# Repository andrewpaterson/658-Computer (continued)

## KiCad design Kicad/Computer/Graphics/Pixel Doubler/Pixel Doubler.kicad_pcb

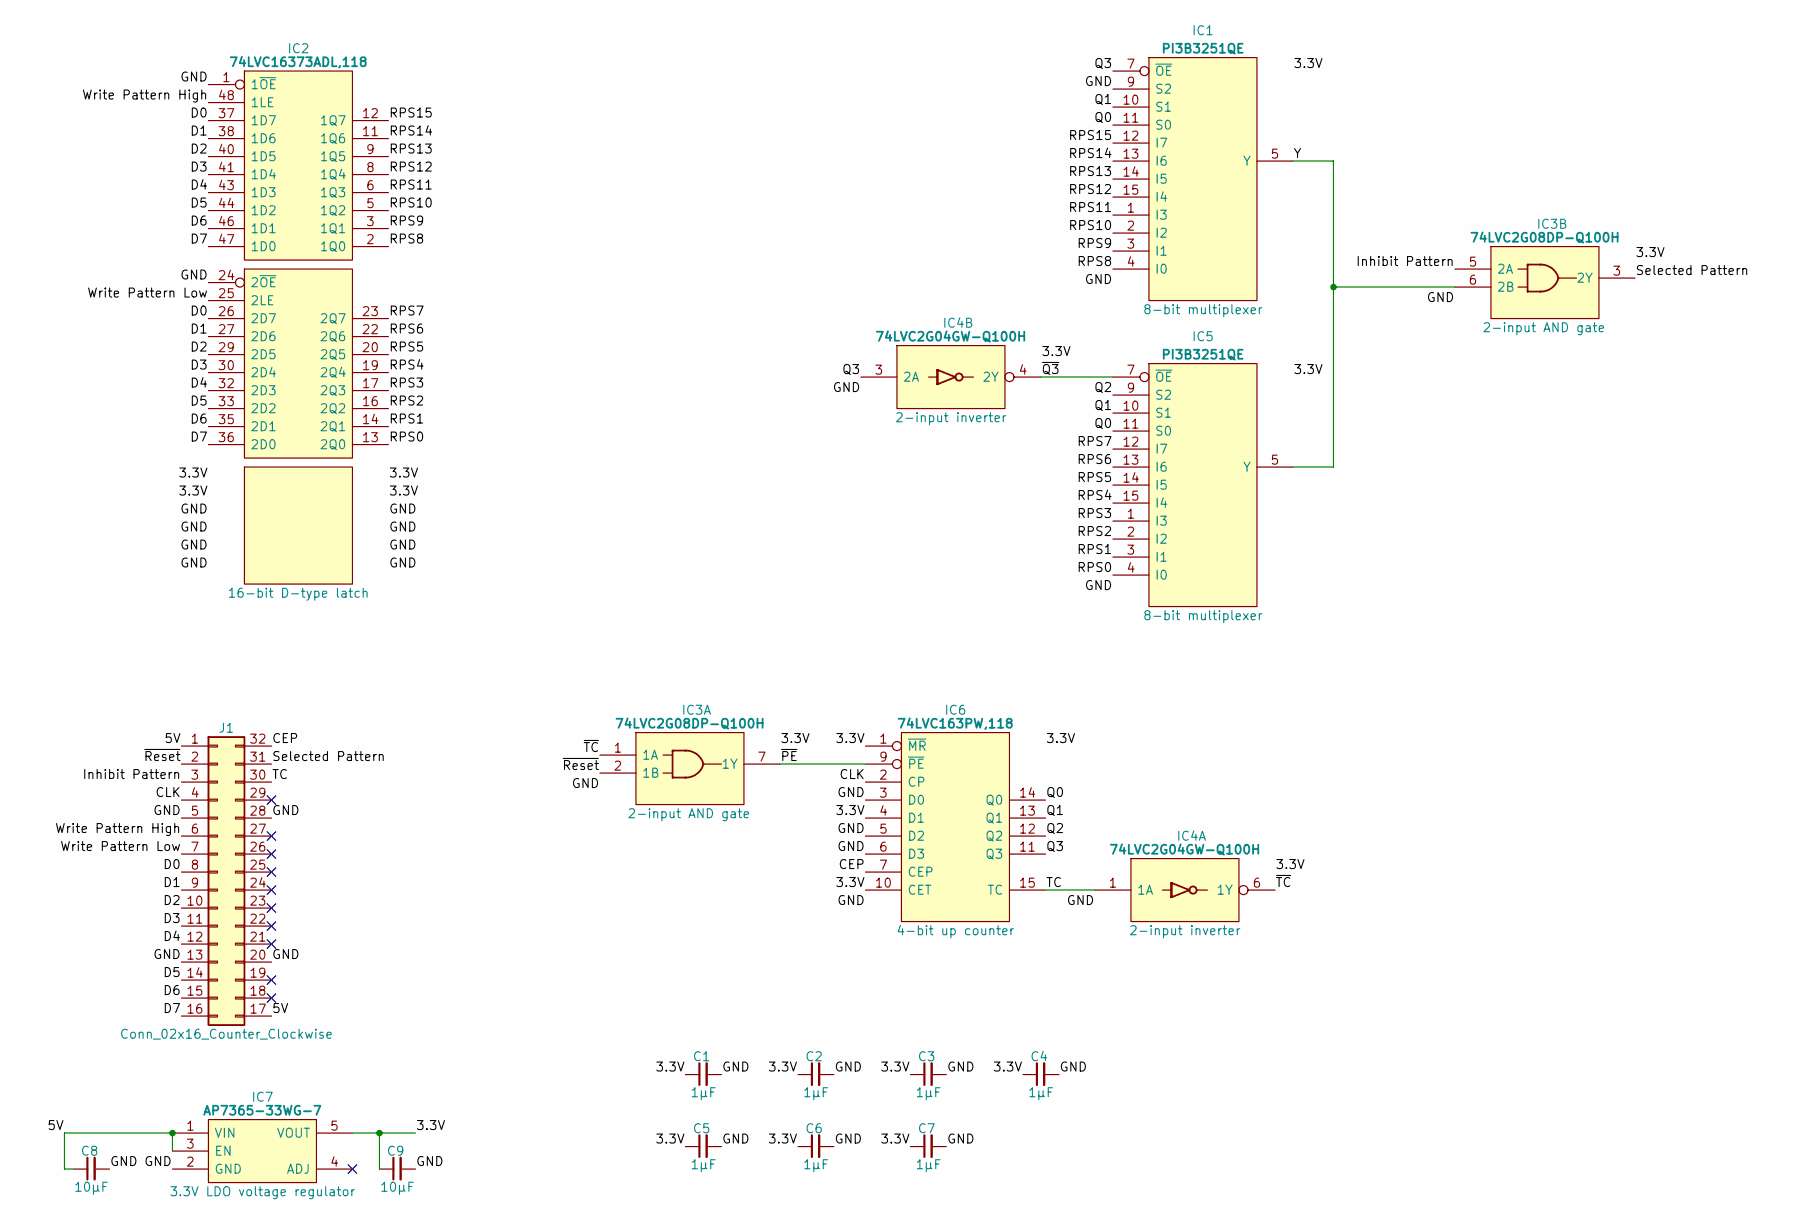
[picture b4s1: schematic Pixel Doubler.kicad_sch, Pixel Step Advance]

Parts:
C1, C2, C3, C4, C5, C6, C7: 1μF; C_0805
C8, C9: 10µF; C_0805
IC1, IC5: PI3B3251QE; SOP64P599X175-16N; Manufacturer_Part_Number PI3B3251QE; Mouser Part Number 729-PI3B3251QE
IC2: 74LVC16373ADL,118; SOP64P1025X280-48N; Mouser Part Number 771-LVC16373ADL118
IC3: 74LVC2G08DP-Q100H; SOP65P400X110-8N; Manufacturer_Part_Number 74LVC2G08DP-Q100H; Mouser Part Number 771-74LVC2G08DPQ100H
IC4: 74LVC2G04GW-Q100H; SOP65P210X110-6N; Manufacturer_Part_Number 74LVC2G04GW-Q100H; Mouser Part Number 771-74LVC2G04GWQ100H
IC6: 74LVC163PW,118; SOP65P640X110-16N; Mouser Part Number 771-74LVC163PW-T
IC7: AP7365-33WG-7; SOT95P285X130-5N; Manufacturer_Part_Number AP7365-33WG-7; Mouser Part Number 621-AP7365-33WG-7
J1: Conn_02x16_Counter_Clockwise; DIP-32_Board_W22.86mm

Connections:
/3.3V: C1.1, C2.1, C3.1, C4.1, C5.1, C6.1, C7.1, C9.1, IC1.16 (3V), IC2.7 (3V), IC2.18 (3V), IC2.31 (3V), IC2.42 (3V), IC3.8 (3V), IC4.5 (3V), IC5.16 (3V), IC6.1 (~MR), IC6.4 (D1), IC6.10 (CET), IC6.16 (3V), IC7.5 (VOUT)
/5V: C8.1, IC7.1 (VIN), IC7.3 (EN), J1.1, J1.17
/CEP: IC6.7 (CEP), J1.32
/CLK: IC6.2 (CP), J1.4
/D0: IC2.26 (2D7), IC2.37 (1D7), J1.8
/D1: IC2.27 (2D6), IC2.38 (1D6), J1.9
/D2: IC2.29 (2D5), IC2.40 (1D5), J1.10
/D3: IC2.30 (2D4), IC2.41 (1D4), J1.11
/D4: IC2.32 (2D3), IC2.43 (1D3), J1.12
/D5: IC2.33 (2D2), IC2.44 (1D2), J1.14
/D6: IC2.35 (2D1), IC2.46 (1D1), J1.15
/D7: IC2.36 (2D0), IC2.47 (1D0), J1.16
/GND: C1.2, C2.2, C3.2, C4.2, C5.2, C6.2, C7.2, C8.2, C9.2, IC1.8 (GND), IC1.9 (S2), IC2.1 (1~OE), IC2.4 (GND), IC2.10 (GND), IC2.15 (GND), IC2.21 (GND), IC2.24 (2~OE), IC2.28 (GND), IC2.34 (GND), IC2.39 (GND), IC2.45 (GND), IC3.4 (GND), IC4.2 (GND), IC5.8 (GND), IC6.3 (D0), IC6.5 (D2), IC6.6 (D3), IC6.8 (GND), IC7.2 (GND), J1.5, J1.13, J1.20, J1.28
/Inhibit Pattern: IC3.5 (2A), J1.3
/Q0: IC1.11 (S0), IC5.11 (S0), IC6.14 (Q0)
/Q1: IC1.10 (S1), IC5.10 (S1), IC6.13 (Q1)
/Q2: IC5.9 (S2), IC6.12 (Q2)
/Q3: IC1.7 (~OE), IC4.3 (2A), IC6.11 (Q3)
/RPS0: IC2.13 (2Q0), IC5.4 (I0)
/RPS1: IC2.14 (2Q1), IC5.3 (I1)
/RPS2: IC2.16 (2Q2), IC5.2 (I2)
/RPS3: IC2.17 (2Q3), IC5.1 (I3)
/RPS4: IC2.19 (2Q4), IC5.15 (I4)
/RPS5: IC2.20 (2Q5), IC5.14 (I5)
/RPS6: IC2.22 (2Q6), IC5.13 (I6)
/RPS7: IC2.23 (2Q7), IC5.12 (I7)
/RPS8: IC1.4 (I0), IC2.2 (1Q0)
/RPS9: IC1.3 (I1), IC2.3 (1Q1)
/RPS10: IC1.2 (I2), IC2.5 (1Q2)
/RPS11: IC1.1 (I3), IC2.6 (1Q3)
/RPS12: IC1.15 (I4), IC2.8 (1Q4)
/RPS13: IC1.14 (I5), IC2.9 (1Q5)
/RPS14: IC1.13 (I6), IC2.11 (1Q6)
/RPS15: IC1.12 (I7), IC2.12 (1Q7)
/Selected Pattern: IC3.3 (2Y), J1.31
/TC: IC4.1 (1A), IC6.15 (TC), J1.30
/Write Pattern High: IC2.48 (1LE), J1.6
/Write Pattern Low: IC2.25 (2LE), J1.7
/Y: IC1.5 (Y), IC3.6 (2B), IC5.5 (Y)
/~PE: IC3.7 (1Y), IC6.9 (~PE)
/~Q3: IC4.4 (2Y), IC5.7 (~OE)
/~Reset: IC3.2 (1B), J1.2
/~TC: IC3.1 (1A), IC4.6 (1Y)

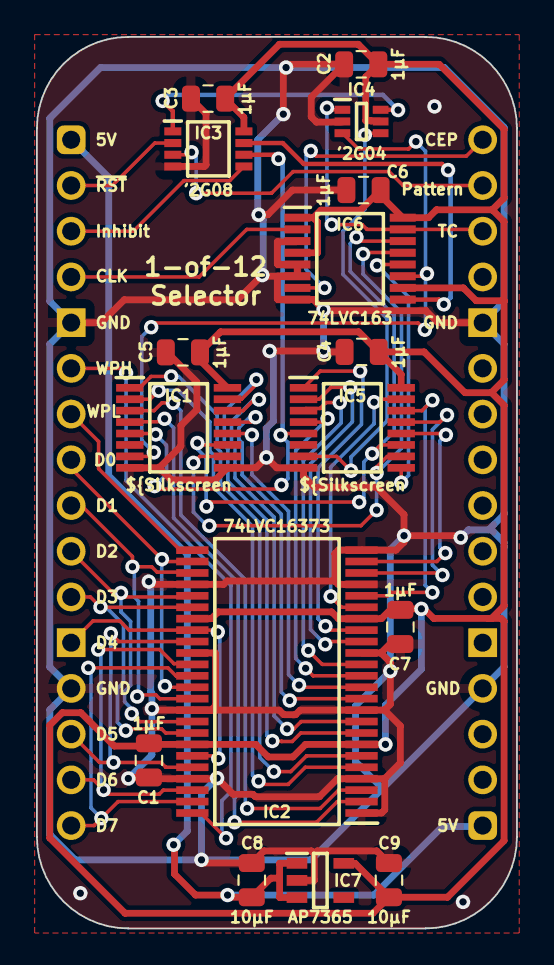
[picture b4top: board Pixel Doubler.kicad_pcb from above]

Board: 2 copper layers, 26.7 x 49.5 mm, 17 parts (0 on the bottom side), 43 nets.

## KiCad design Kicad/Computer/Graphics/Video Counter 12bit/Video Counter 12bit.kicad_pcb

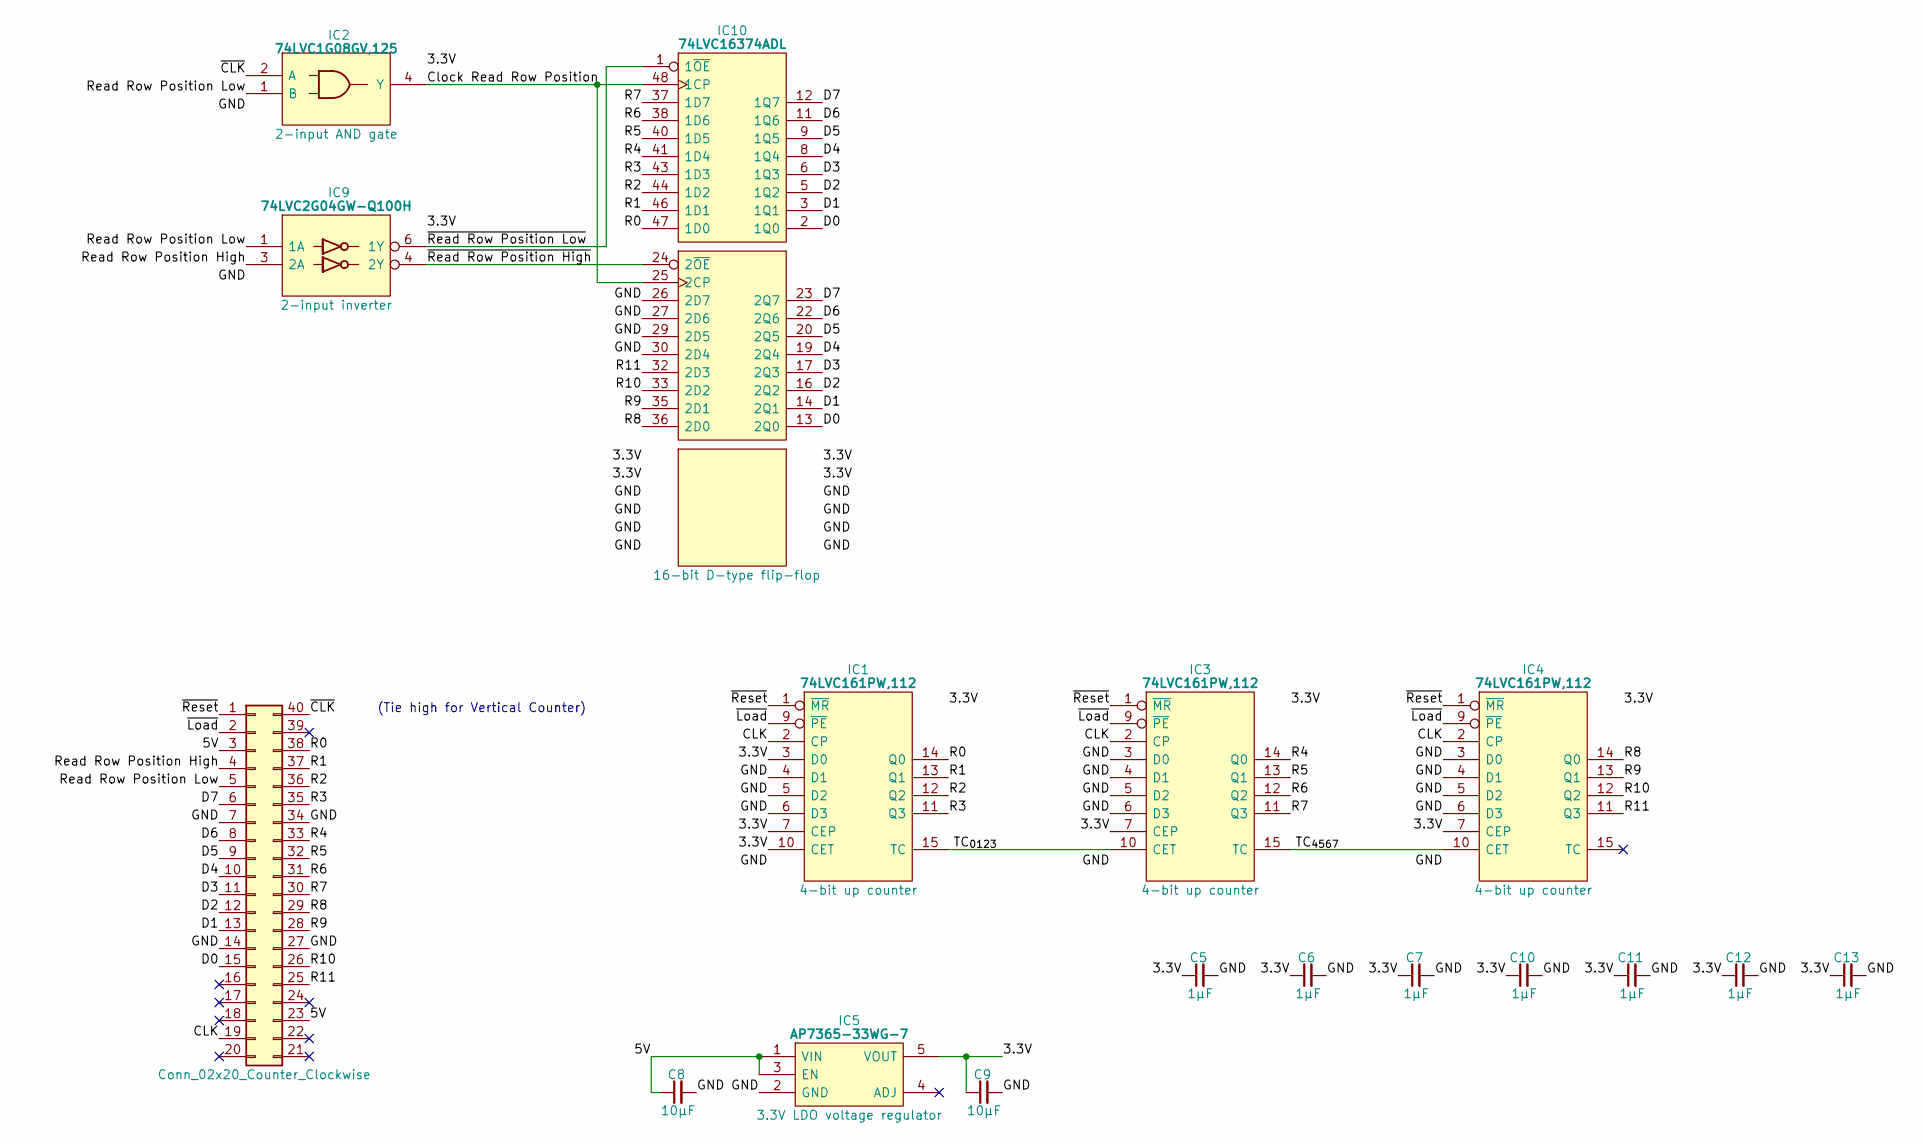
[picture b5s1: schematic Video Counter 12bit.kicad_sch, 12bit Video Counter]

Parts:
C5, C6, C7, C10, C11, C12, C13: 1μF; C_0805
C8, C9: 10µF; C_0805
IC1, IC3, IC4: 74LVC161PW,112; SOP65P640X110-16N; Mouser Part Number 771-LVC161PW112
IC2: 74LVC1G08GV,125; SOT95P275X110-5N; Manufacturer_Part_Number 74LVC1G08GV,125; Mouser Part Number 771-74LVC1G08GV
IC5: AP7365-33WG-7; SOT95P285X130-5N; Manufacturer_Part_Number AP7365-33WG-7; Mouser Part Number 621-AP7365-33WG-7
IC9: 74LVC2G04GW-Q100H; SOP65P210X110-6N; Manufacturer_Part_Number 74LVC2G04GW-Q100H; Mouser Part Number 771-74LVC2G04GWQ100H
IC10: 74LVC16374ADL; SOP64P1025X280-48N; Manufacturer_Part_Number 74LVC16374ADL; Mouser Part Number 771-74LVC16374ADL
J3: Conn_02x20_Counter_Clockwise; DIP-40_Board_W15.24mm

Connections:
/3.3V: C5.1, C6.1, C7.1, C9.1, C10.1, C11.1, C12.1, C13.1, IC1.3 (D0), IC1.7 (CEP), IC1.10 (CET), IC1.16 (3V), IC2.5 (3V), IC3.7 (CEP), IC3.16 (3V), IC4.7 (CEP), IC4.16 (3V), IC5.5 (VOUT), IC9.5 (3V), IC10.7 (3V), IC10.18 (3V), IC10.31 (3V), IC10.42 (3V)
/5V: C8.1, IC5.1 (VIN), IC5.3 (EN), J3.3, J3.23
/CLK: IC1.2 (CP), IC3.2 (CP), IC4.2 (CP), J3.19
/Clock Read Row Position: IC2.4 (Y), IC10.25 (2CP), IC10.48 (1CP)
/D0: IC10.2 (1Q0), IC10.13 (2Q0), J3.15
/D1: IC10.3 (1Q1), IC10.14 (2Q1), J3.13
/D2: IC10.5 (1Q2), IC10.16 (2Q2), J3.12
/D3: IC10.6 (1Q3), IC10.17 (2Q3), J3.11
/D4: IC10.8 (1Q4), IC10.19 (2Q4), J3.10
/D5: IC10.9 (1Q5), IC10.20 (2Q5), J3.9
/D6: IC10.11 (1Q6), IC10.22 (2Q6), J3.8
/D7: IC10.12 (1Q7), IC10.23 (2Q7), J3.6
/GND: C5.2, C6.2, C7.2, C8.2, C9.2, C10.2, C11.2, C12.2, C13.2, IC1.4 (D1), IC1.5 (D2), IC1.6 (D3), IC1.8 (GND), IC2.3 (GND), IC3.3 (D0), IC3.4 (D1), IC3.5 (D2), IC3.6 (D3), IC3.8 (GND), IC4.3 (D0), IC4.4 (D1), IC4.5 (D2), IC4.6 (D3), IC4.8 (GND), IC5.2 (GND), IC9.2 (GND), IC10.4 (GND), IC10.10 (GND), IC10.15 (GND), IC10.21 (GND), IC10.26 (2D7), IC10.27 (2D6), IC10.28 (GND), IC10.29 (2D5), IC10.30 (2D4), IC10.34 (GND), IC10.39 (GND), IC10.45 (GND), J3.7, J3.14, J3.27, J3.34
/R0: IC1.14 (Q0), IC10.47 (1D0), J3.38
/R1: IC1.13 (Q1), IC10.46 (1D1), J3.37
/R2: IC1.12 (Q2), IC10.44 (1D2), J3.36
/R3: IC1.11 (Q3), IC10.43 (1D3), J3.35
/R4: IC3.14 (Q0), IC10.41 (1D4), J3.33
/R5: IC3.13 (Q1), IC10.40 (1D5), J3.32
/R6: IC3.12 (Q2), IC10.38 (1D6), J3.31
/R7: IC3.11 (Q3), IC10.37 (1D7), J3.30
/R8: IC4.14 (Q0), IC10.36 (2D0), J3.29
/R9: IC4.13 (Q1), IC10.35 (2D1), J3.28
/R10: IC4.12 (Q2), IC10.33 (2D2), J3.26
/R11: IC4.11 (Q3), IC10.32 (2D3), J3.25
/Read Row Position High: IC9.3 (2A), J3.4
/Read Row Position Low: IC2.1 (B), IC9.1 (1A), J3.5
/TC_{0123}: IC1.15 (TC), IC3.10 (CET)
/TC_{4567}: IC3.15 (TC), IC4.10 (CET)
/~CLK: IC2.2 (A), J3.40
/~Load: IC1.9 (~PE), IC3.9 (~PE), IC4.9 (~PE), J3.2
/~Read Row Position High: IC9.4 (2Y), IC10.24 (2~OE)
/~Read Row Position Low: IC9.6 (1Y), IC10.1 (1~OE)
/~Reset: IC1.1 (~MR), IC3.1 (~MR), IC4.1 (~MR), J3.1

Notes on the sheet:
(Tie high for Vertical Counter)

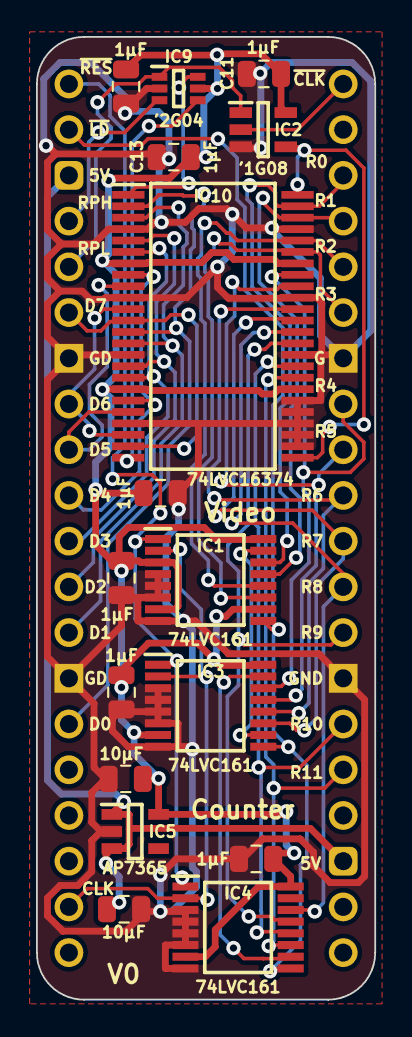
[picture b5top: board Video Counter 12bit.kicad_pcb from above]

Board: 2 copper layers, 18.8 x 53.5 mm, 17 parts (0 on the bottom side), 34 nets.

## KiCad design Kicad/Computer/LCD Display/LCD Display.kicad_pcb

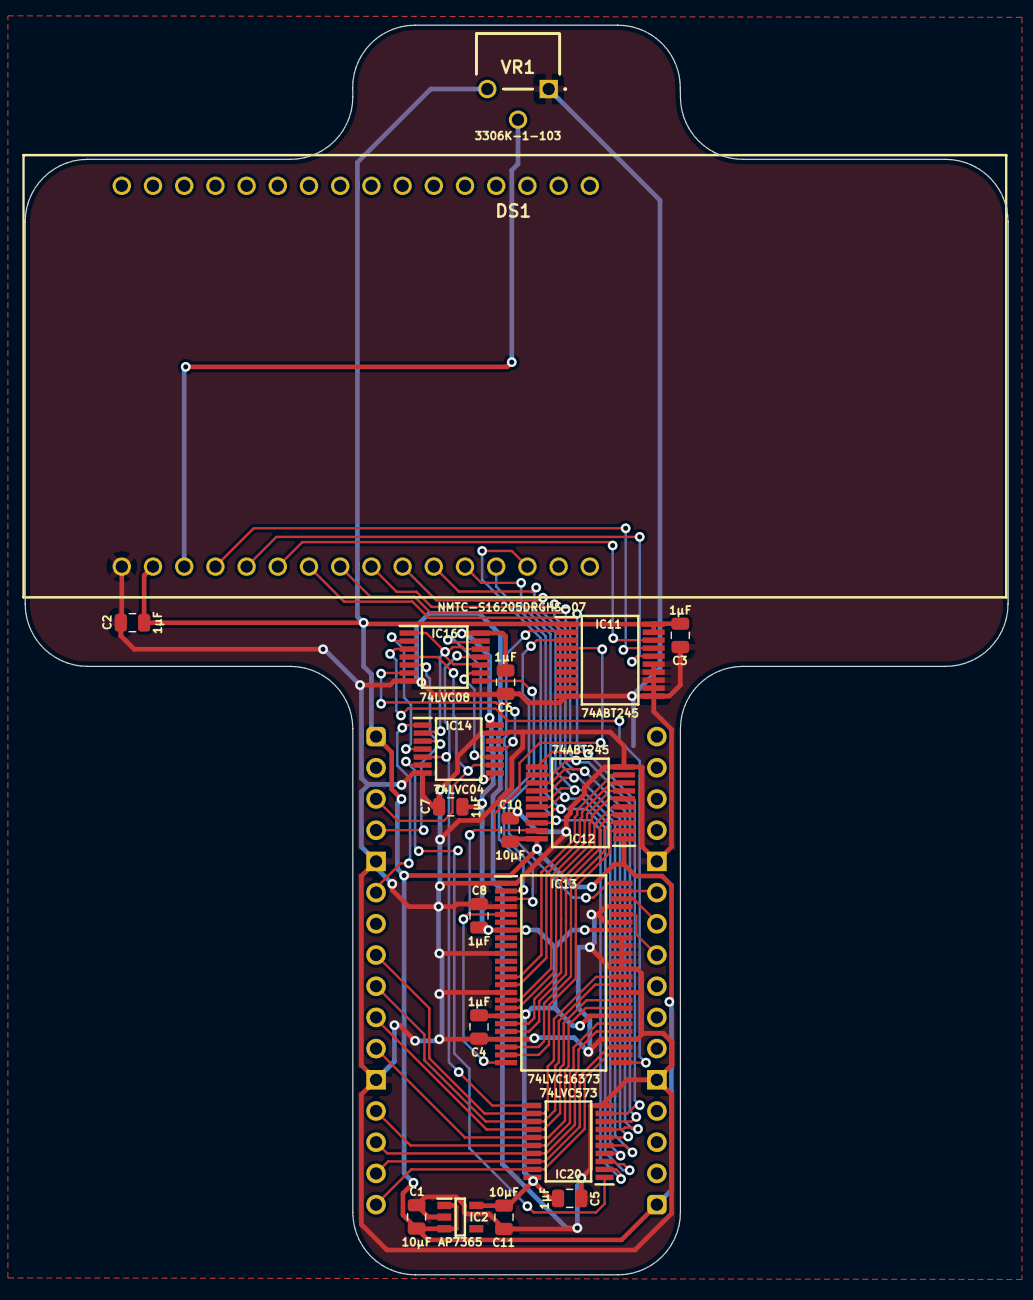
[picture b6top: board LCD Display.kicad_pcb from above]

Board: 2 copper layers, 80.0 x 101.7 mm, 20 parts (0 on the bottom side), 49 nets.

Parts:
C1, C10, C11: 10μF; C_0805
C2, C3, C4, C5, C6, C7, C8: 1μF; C_0805
DS1: NMTC-S16205DRGHS-07; NMTCS16205DRGHS07_1
IC2: AP7365-33WG-7; SOT95P285X130-5N
IC11, IC12: SN74ABT245BDBR; SOP65P780X200-20N
IC13: 74LVC16373ADL,118; SOP64P1025X280-48N
IC14: 74LVC04APW,118; SOP65P640X110-14N
IC16: 74LVC08APW,112; SOP65P640X110-14N
IC20: 74LVC573APW,118; SOP65P640X110-20N
J1: Conn_02x16_Counter_Clockwise; DIP-32_Board_W22.86mm_Nak
VR1: 3306K-1-103; 3306K1103

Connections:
/3.3V: C4.1, C5.1, C6.1, C7.1, C8.1, C11.1, IC2.5 (VOUT), IC13.7 (3V), IC13.18 (3V), IC13.31 (3V), IC13.42 (3V), IC14.14 (3V), IC16.14 (3V), IC20.20 (3V)
/5V: C1.1, C2.1, C3.1, C10.1, DS1.2 (5V), IC2.1 (VIN), IC2.3 (EN), IC11.1 (DIR), IC11.19 (~OE), IC11.20 (5V), IC12.1 (DIR), IC12.20 (5V), J1.1, J1.17, VR1.3 (VIN)
/(RD+WD)·CS: IC13.48 (1LE), IC16.8 (3Y)
/A0: IC13.47 (1D0), J1.27
/A1: IC13.46 (1D1), J1.26
/A2: IC13.44 (1D2), J1.25
/CS: IC14.2 (1Y), IC16.1 (1A), IC16.10 (3B), IC16.12 (4A)
/D0: IC13.36 (2D0), IC20.12 (Q7), J1.8
/D0_{Latch}: IC12.9 (A7), IC13.13 (2Q0)
/D1: IC13.35 (2D1), IC20.13 (Q6), J1.9
/D1_{Latch}: IC12.8 (A6), IC13.14 (2Q1)
/D2: IC13.33 (2D2), IC20.14 (Q5), J1.10
/D2_{Latch}: IC12.7 (A5), IC13.16 (2Q2)
/D3: IC13.32 (2D3), IC20.15 (Q4), J1.11
/D3_{Latch}: IC12.6 (A4), IC13.17 (2Q3)
/D4: IC13.30 (2D4), IC20.16 (Q3), J1.13
/D4_{Latch}: IC12.5 (A3), IC13.19 (2Q4)
/D5: IC13.29 (2D5), IC20.17 (Q2), J1.14
/D5_{Latch}: IC12.4 (A2), IC13.20 (2Q5)
/D6: IC13.27 (2D6), IC20.18 (Q1), J1.15
/D6_{Latch}: IC12.3 (A1), IC13.22 (2Q6)
/D7: IC13.26 (2D7), IC20.19 (Q0), J1.16
/D7_{Latch}: IC12.2 (A0), IC13.23 (2Q7)
/DB0: DS1.7 (DB0), IC12.11 (B7), IC20.9 (D7)
/DB1: DS1.8 (DB1), IC12.12 (B6), IC20.8 (D6)
/DB2: DS1.9 (DB2), IC12.13 (B5), IC20.7 (D5)
/DB3: DS1.10 (DB3), IC12.14 (B4), IC20.6 (D4)
/DB4: DS1.11 (DB4), IC12.15 (B3), IC20.5 (D3)
/DB5: DS1.12 (DB5), IC12.16 (B2), IC20.4 (D2)
/DB6: DS1.13 (DB6), IC12.17 (B1), IC20.3 (D1)
/DB7: DS1.14 (DB7), IC12.18 (B0), IC20.2 (D0)
/Device ~CS: IC14.1 (1A), J1.6
/E: DS1.6 (E), IC11.18 (B0)
/E_{Latch}: IC11.2 (A0), IC13.2 (1Q0)
/GND: C1.2, C2.2, C3.2, C4.2, C5.2, C6.2, C7.2, C8.2, C10.2, C11.2, DS1.1 (GND), IC2.2 (GND), IC11.10 (GND), IC11.11 (B7), IC11.12 (B6), IC11.13 (B5), IC11.14 (B4), IC11.15 (B3), IC12.10 (GND), IC13.1 (1~OE), IC13.4 (GND), IC13.10 (GND), IC13.15 (GND), IC13.21 (GND), IC13.28 (GND), IC13.34 (GND), IC13.37 (1D7), IC13.38 (1D6), IC13.39 (GND), IC13.40 (1D5), IC13.41 (1D4), IC13.43 (1D3), IC13.45 (GND), IC14.7 (GND), IC14.13 (6A), IC16.7 (GND), IC20.10 (GND), J1.5, J1.12, J1.21, J1.28, VR1.1 (GND)
/RD: IC14.8 (4Y), IC16.13 (4B)
/RD+WD: IC14.10 (5Y), IC16.9 (3A)
/RD·CS: IC14.5 (3A), IC16.11 (4Y), IC20.11 (LE)
/RS: DS1.4 (RS), IC11.17 (B1)
/RS_{Latch}: IC11.3 (A1), IC13.3 (1Q1)
/R~W: DS1.5 (R/~W), IC11.16 (B2)
/R~W_{Latch}: IC11.4 (A2), IC12.19 (~OE), IC13.5 (1Q2), IC13.24 (2~OE)
/V_{0}: DS1.3 (V_{O}), VR1.2 (VOUT)
/WD: IC14.4 (2Y), IC16.2 (1B)
/WD·CS: IC13.25 (2LE), IC16.3 (1Y)
/~RD: IC14.9 (4A), IC16.4 (2A), J1.3
/~RD+~CS: IC14.6 (3Y), IC20.1 (~OE)
/~RD·~WD: IC14.11 (5A), IC16.6 (2Y)
/~WD: IC14.3 (2A), IC16.5 (2B), J1.4

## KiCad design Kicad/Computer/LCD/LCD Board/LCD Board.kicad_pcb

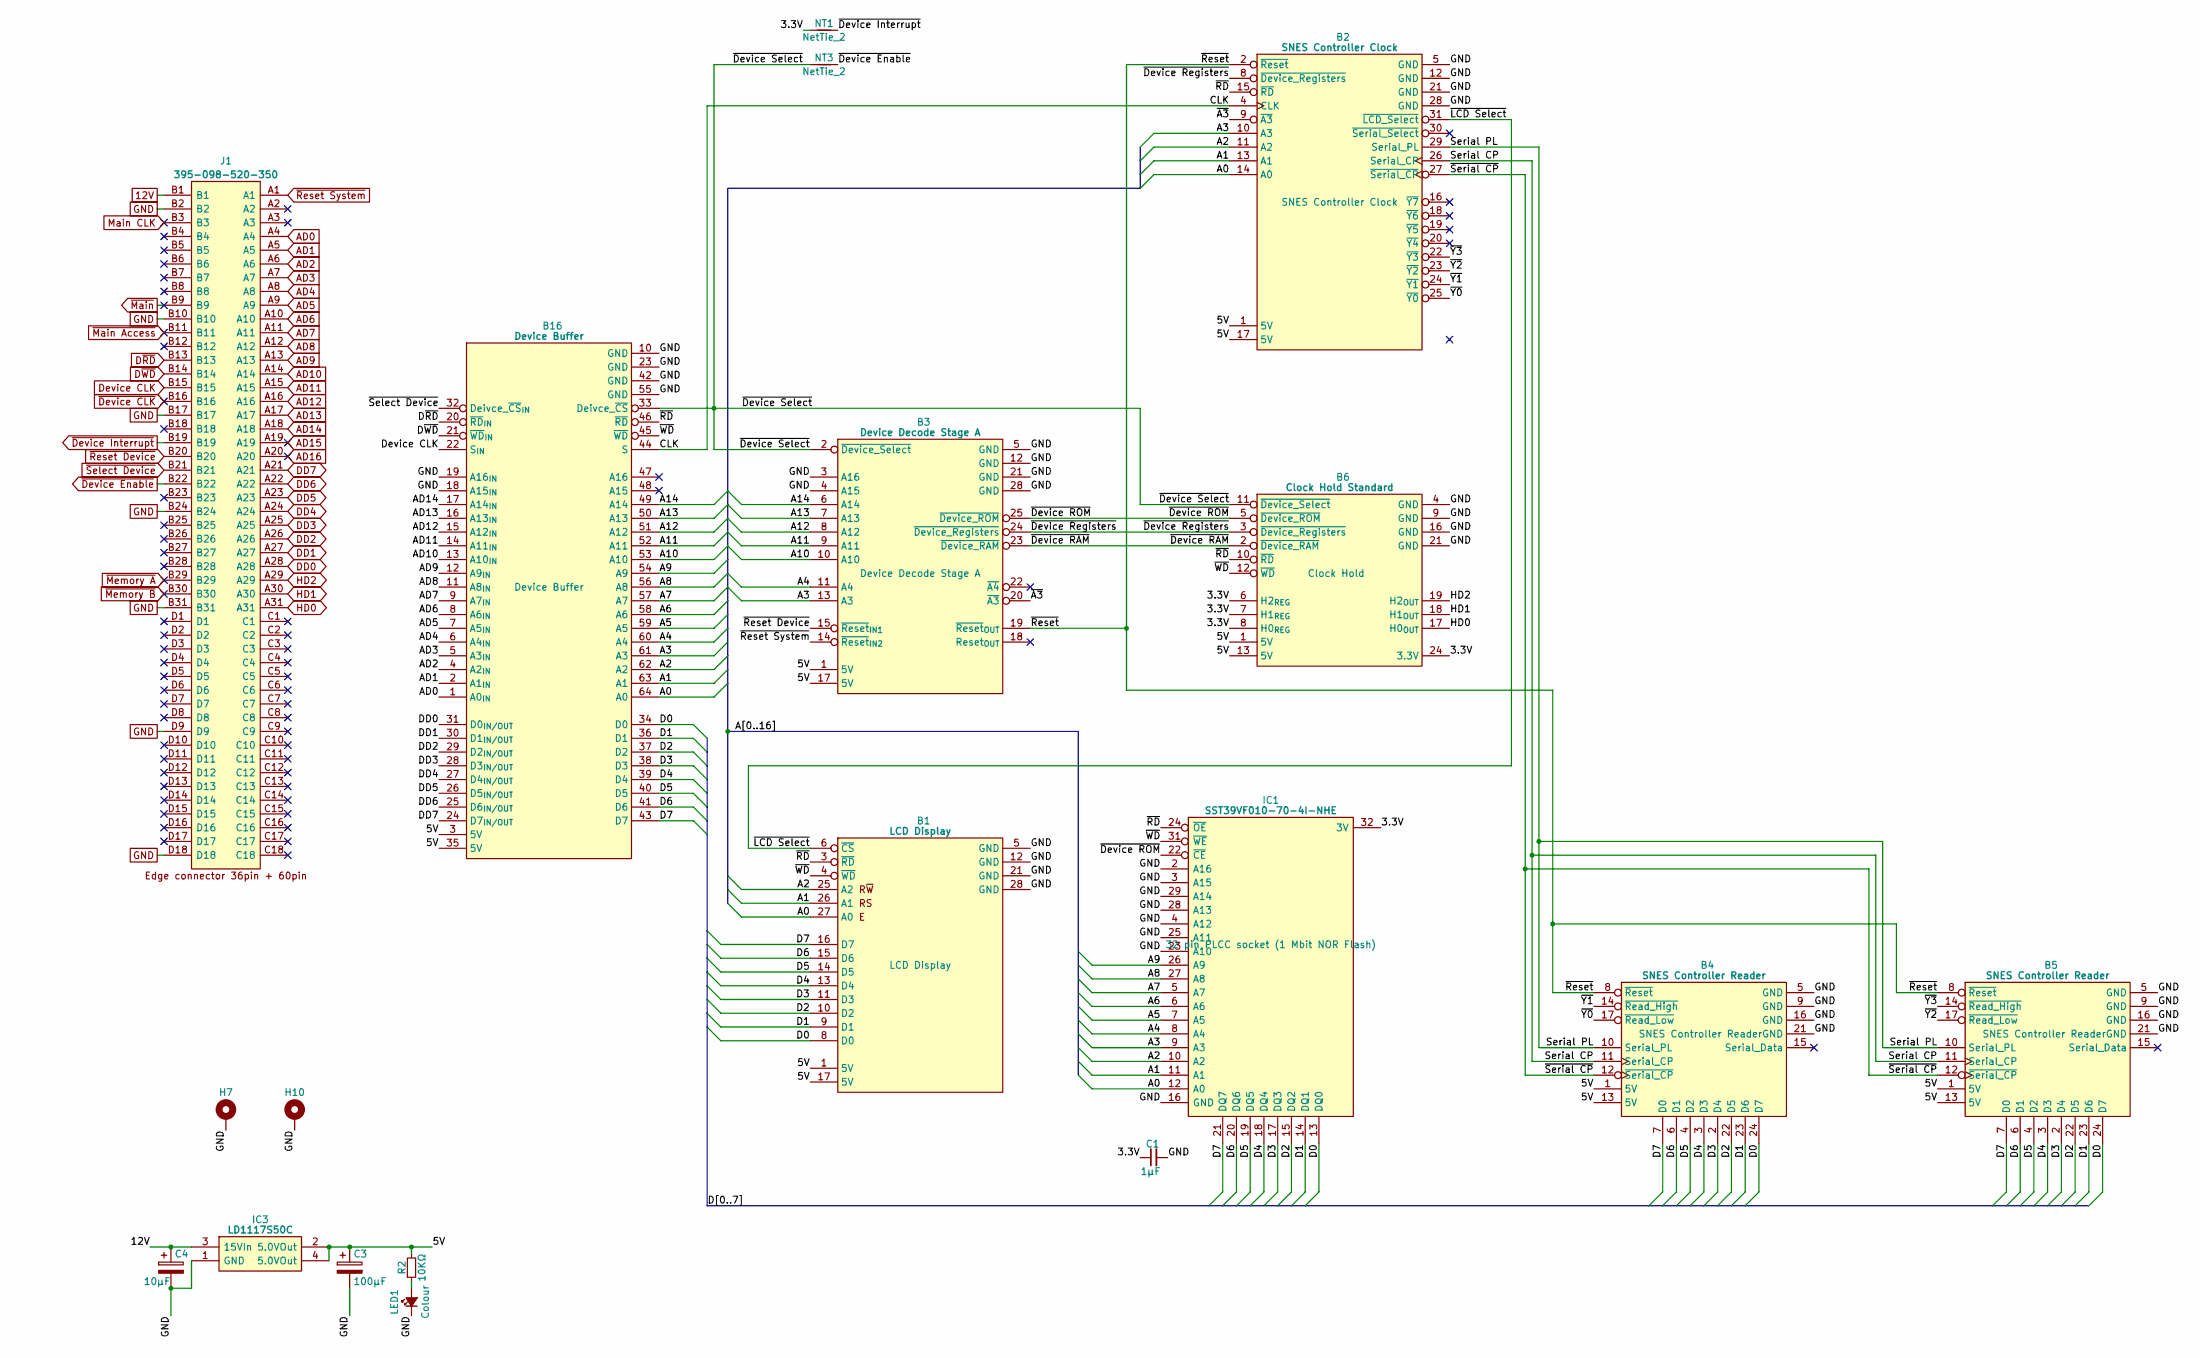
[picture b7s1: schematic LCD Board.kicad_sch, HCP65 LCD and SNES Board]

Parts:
B1: LCD Display; HCP65_LCD_Display
B2: SNES Controller Clock; HCP65_SNES_Controller_Clock
B3: Device Decode Stage A; HCP65_Device_Decode_Stage_A
B4, B5: SNES Controller Reader; HCP65_SNES_Controller_Reader
B6: Clock Hold Standard; HCP65_Clock_Hold_Standard
B16: Device Buffer; HCP65_Device_Buffer
C1: 1µF; C_0805
C3: 100μF; CP_Radial_D4.0mm_P2.00mm
C4: 10μF; CP_Radial_D4.0mm_P2.00mm
H7, H10: MountingHole_Pad; HCP65_MountingHole_M3_
IC1: SST39VF010-70-4I-NHE; 5408803224008; Manufacturer_Part_Number SST39VF010-70-4I-NHE
IC3: LD1117S50C; LD1117S33C; Manufacturer_Part_Number LD1117S50C
J1: 395-098-520-350; 98pin Edge Connector; Manufacturer_Part_Number 395-098-520-350; Mouser Part Number 587-395-098-520-350
LED1: Colour; LED_D5.0mm
NT1, NT3: NetTie_2; NetTie-2_SMD_Pad0.5mm
R2: 10KΩ; R_0805

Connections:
12V: C4.1, IC3.3 (15VIn), J1.B1
/3.3V: B6.6 (H2_{REG}), B6.7 (H1_{REG}), B6.8 (H0_{REG}), B6.24 (3.3V), C1.1, IC1.32 (3V), NT1.2
/5V: B1.1 (5V), B1.17 (5V), B2.1 (5V), B2.17 (5V), B3.1 (5V), B3.17 (5V), B4.1 (5V), B4.13 (5V), B5.1 (5V), B5.13 (5V), B6.1 (5V), B6.13 (5V), B16.3 (5V), B16.35 (5V), C3.1, IC3.2 (5.0VOut), IC3.4 (5.0VOut), R2.2
/A0: B1.27 (A0), B2.14 (A0), B16.64 (A0), IC1.12 (A0)
/A1: B1.26 (A1), B2.13 (A1), B16.63 (A1), IC1.11 (A1)
/A2: B1.25 (A2), B2.11 (A2), B16.62 (A2), IC1.10 (A2)
/A3: B2.10 (A3), B3.13 (A3), B16.61 (A3), IC1.9 (A3)
/A4: B3.11 (A4), B16.60 (A4), IC1.8 (A4)
/A5: B16.59 (A5), IC1.7 (A5)
/A6: B16.58 (A6), IC1.6 (A6)
/A7: B16.57 (A7), IC1.5 (A7)
/A8: B16.56 (A8), IC1.27 (A8)
/A9: B16.54 (A9), IC1.26 (A9)
/A10: B3.10 (A10), B16.53 (A10)
/A11: B3.9 (A11), B16.52 (A11)
/A12: B3.8 (A12), B16.51 (A12)
/A13: B3.7 (A13), B16.50 (A13)
/A14: B3.6 (A14), B16.49 (A14)
/CLK: B2.4 (CLK), B16.44 (S)
/D0: B1.8 (D0), B4.24 (D7), B5.24 (D7), B16.34 (D0), IC1.13 (DQ0)
/D1: B1.9 (D1), B4.23 (D6), B5.23 (D6), B16.36 (D1), IC1.14 (DQ1)
/D2: B1.10 (D2), B4.22 (D5), B5.22 (D5), B16.37 (D2), IC1.15 (DQ2)
/D3: B1.11 (D3), B4.2 (D4), B5.2 (D4), B16.38 (D3), IC1.17 (DQ3)
/D4: B1.13 (D4), B4.3 (D3), B5.3 (D3), B16.39 (D4), IC1.18 (DQ4)
/D5: B1.14 (D5), B4.4 (D2), B5.4 (D2), B16.40 (D5), IC1.19 (DQ5)
/D6: B1.15 (D6), B4.6 (D1), B5.6 (D1), B16.41 (D6), IC1.20 (DQ6)
/D7: B1.16 (D7), B4.7 (D0), B5.7 (D0), B16.43 (D7), IC1.21 (DQ7)
/Serial CP: B2.26 (Serial_CP), B4.11 (Serial_CP), B5.11 (Serial_CP)
/Serial PL: B2.29 (Serial_PL), B4.10 (Serial_PL), B5.10 (Serial_PL)
/~A3: B2.9 (~A3), B3.20 (~A3)
/~Device RAM: B3.23 (~Device_RAM), B6.2 (~Device_RAM)
/~Device ROM: B3.25 (~Device_ROM), B6.5 (~Device_ROM), IC1.22 (~CE)
/~Device Registers: B2.8 (~Device_Registers), B3.24 (~Device_Registers), B6.3 (~Device_Registers)
/~Device Select: B3.2 (~Device_Select), B6.11 (~Device_Select), B16.33 (Deivce_~CS), NT3.2
/~LCD Select: B1.6 (~CS), B2.31 (~LCD_Select)
/~RD: B1.3 (~RD), B2.15 (~RD), B6.10 (~RD), B16.46 (~RD), IC1.24 (~OE)
/~Reset: B2.2 (~Reset), B3.19 (~Reset_{OUT}), B4.8 (~Reset), B5.8 (~Reset)
/~Serial CP: B2.27 (~Serial_CP), B4.12 (~Serial_CP), B5.12 (~Serial_CP)
/~WD: B1.4 (~WD), B6.12 (~WD), B16.45 (~WD), IC1.31 (~WE)
/~Y0: B2.25 (~Y0), B4.17 (~Read_Low)
/~Y1: B2.24 (~Y1), B4.14 (~Read_High)
/~Y2: B2.23 (~Y2), B5.17 (~Read_Low)
/~Y3: B2.22 (~Y3), B5.14 (~Read_High)
AD0: B16.1 (A0_{IN}), J1.A4
AD1: B16.2 (A1_{IN}), J1.A5
AD2: B16.4 (A2_{IN}), J1.A6
AD3: B16.5 (A3_{IN}), J1.A7
AD4: B16.6 (A4_{IN}), J1.A8
AD5: B16.7 (A5_{IN}), J1.A9
AD6: B16.8 (A6_{IN}), J1.A10
AD7: B16.9 (A7_{IN}), J1.A11
AD8: B16.11 (A8_{IN}), J1.A12
AD9: B16.12 (A9_{IN}), J1.A13
AD10: B16.13 (A10_{IN}), J1.A14
AD11: B16.14 (A11_{IN}), J1.A15
AD12: B16.15 (A12_{IN}), J1.A16
AD13: B16.16 (A13_{IN}), J1.A17
AD14: B16.17 (A14_{IN}), J1.A18
AD15: J1.A19
AD16: J1.A20
DD0: B16.31 (D0_{IN/OUT}), J1.A28
DD1: B16.30 (D1_{IN/OUT}), J1.A27
DD2: B16.29 (D2_{IN/OUT}), J1.A26
DD3: B16.28 (D3_{IN/OUT}), J1.A25
DD4: B16.27 (D4_{IN/OUT}), J1.A24
DD5: B16.26 (D5_{IN/OUT}), J1.A23
DD6: B16.25 (D6_{IN/OUT}), J1.A22
DD7: B16.24 (D7_{IN/OUT}), J1.A21
Device CLK: B16.22 (S_{IN}), J1.B15
D~RD: B16.20 (~RD_{IN}), J1.B13
D~WD: B16.21 (~WD_{IN}), J1.B14
GND: B1.5 (GND), B1.12 (GND), B1.21 (GND), B1.28 (GND), B2.5 (GND), B2.12 (GND), B2.21 (GND), B2.28 (GND), B3.3 (A16), B3.4 (A15), B3.5 (GND), B3.12 (GND), B3.21 (GND), B3.28 (GND), B4.5 (GND), B4.9 (GND), B4.16 (GND), B4.21 (GND), B5.5 (GND), B5.9 (GND), B5.16 (GND), B5.21 (GND), B6.4 (GND), B6.9 (GND), B6.16 (GND), B6.21 (GND), B16.10 (GND), B16.18 (A15_{IN}), B16.19 (A16_{IN}), B16.23 (GND), B16.42 (GND), B16.55 (GND), C1.2, C3.2, C4.2, H7.1 (GND), H10.1 (GND), IC1.2 (A16), IC1.3 (A15), IC1.4 (A12), IC1.16 (GND), IC1.23 (A10), IC1.25 (A11), IC1.28 (A13), IC1.29 (A14), IC3.1 (GND), J1.B2, J1.B10, J1.B17, J1.B24, J1.B31, J1.D9, J1.D18, LED1.1 (K)
HD0: B6.17 (H0_{OUT}), J1.A31
HD1: B6.18 (H1_{OUT}), J1.A30
HD2: B6.19 (H2_{OUT}), J1.A29
Main CLK: J1.B3
unnamed: LED1.2 (A), R2.1
~Device CLK: J1.B16
~Device Enable: J1.B22, NT3.1
~Device Interrupt: J1.B19, NT1.1
~Main Access: J1.B11
~Main: J1.B9
~Memory A: J1.B29
~Memory B: J1.B30
~Reset Device: B3.15 (~Reset_{IN1}), J1.B20
~Reset System: B3.14 (~Reset_{IN2}), J1.A1
~Select Device: B16.32 (Deivce_~CS_{IN}), J1.B21

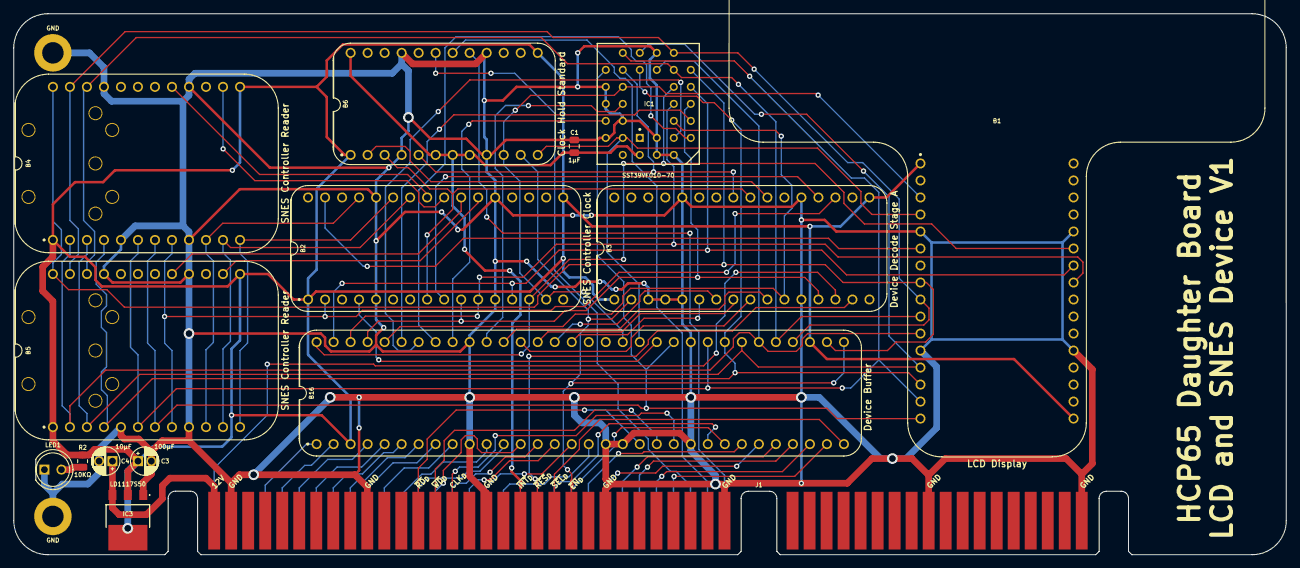
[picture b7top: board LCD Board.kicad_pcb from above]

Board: 2 copper layers, 190.0 x 80.8 mm, 19 parts (0 on the bottom side), 79 nets.
